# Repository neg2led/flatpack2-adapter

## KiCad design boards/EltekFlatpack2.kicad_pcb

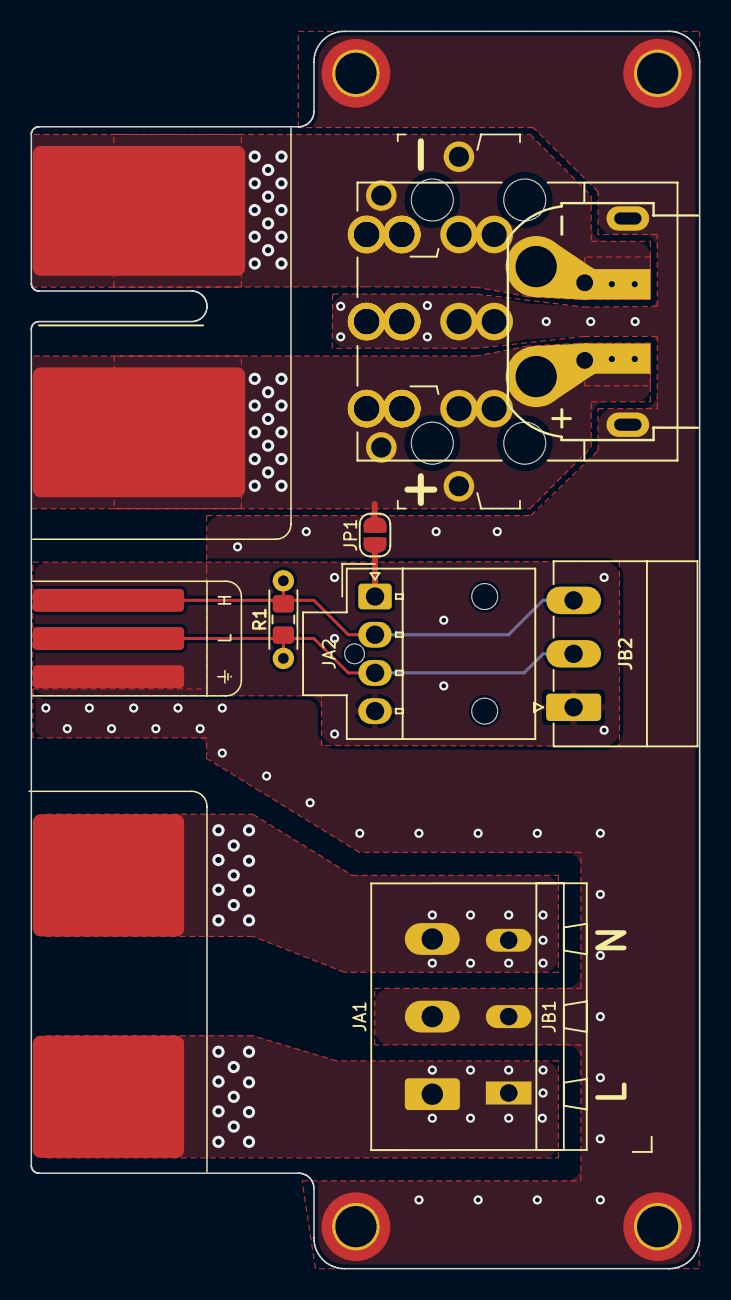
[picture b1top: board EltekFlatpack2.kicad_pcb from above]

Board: 2 copper layers, 43.8 x 81.0 mm, 17 parts (0 on the bottom side), 9 nets.

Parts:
H1, H2, H3, H4: M3; MountingHole_2.7mm_M2.5_ISO7380_Pad_TopBottom
JA1: AC_IN; 1605540000
JA2: CTRL; Molex_Nano-Fit_105309-xx04_1x04_P2.50mm_Combi_3D-V
JA3: DC OUT; TE_2204529-1
JB1: AC_IN; TerminalBlock_WAGO_236-103_1x03_P5.00mm_PadsOnly
JB2: CANBUS; PhoenixContact_MC_1,5_3-G-3.5_1x03_P3.50mm_Horizontal
JB3: DC OUT; TE_2204535-1
JC3: DC OUT; Amass_XT60PW-M_Kombifootprint
JP1: CTRL_VBUS+; SolderJumper-2_P1.3mm_Open_RoundedPad1.0x1.5mm
PC1: Flatpack2; CON_Edge_Flatpack2_AllContacts
R1: 120R; R_0805_2012Metric_Pad1.15x1.40mm_HandSolder
R2: 120R; R_Axial_DIN0204_L3.6mm_D1.6mm_P5.08mm_Horizontal
T1, T2: Keystone 4912; Connector_Keystone_4912_Overlaid

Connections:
Board_1-/CAN+: JA2.2, JB2.3, PC1.CAN-H, R1.2, R2.2
Board_1-/CAN-: JA2.3, JB2.2, PC1.CAN-L, R1.1, R2.1
Board_1-/VBUS+: JA3.1, JB3.1, JB3.4, JC3.2, JP1.1, PC1.DC-POS, T1.1
Board_1-/VBUS-: JA3.3, JB3.3, JB3.6, JC3.1, PC1.DC-NEG, T2.1
Board_1-/VCCD: JA2.1, JP1.2
Board_1-Earth: H1.1, H2.1, H3.1, H4.1, JA1.2, JA3.2, JB1.2, JB3.2, JB3.5, JC3.MP, PC1.AC-E
Board_1-GNDD: JA2.4, JB2.1, PC1.GNDD
Board_1-LINE: JA1.1, JB1.1, PC1.AC-L
Board_1-NEUT: JA1.3, JB1.3, PC1.AC-N

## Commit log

2021-02-10 initial
2021-02-10 fix travis and makefile
2021-02-10 added dimensions
2021-02-10 fix makefile/panel/footprint (now has 1mm mill hole and straight edges!)
2021-02-12 panel of 2, not panel of 3
2021-02-27 add THT termination resistor option
2021-03-01 add keystone tab option
2021-03-01 fix repo path in makefile
2021-03-08 remove dumb log file
2021-03-08 Deploy neg2led/flatpack2-adapter to github.com/neg2led/flatpack2-adapter.git:gh-pages
